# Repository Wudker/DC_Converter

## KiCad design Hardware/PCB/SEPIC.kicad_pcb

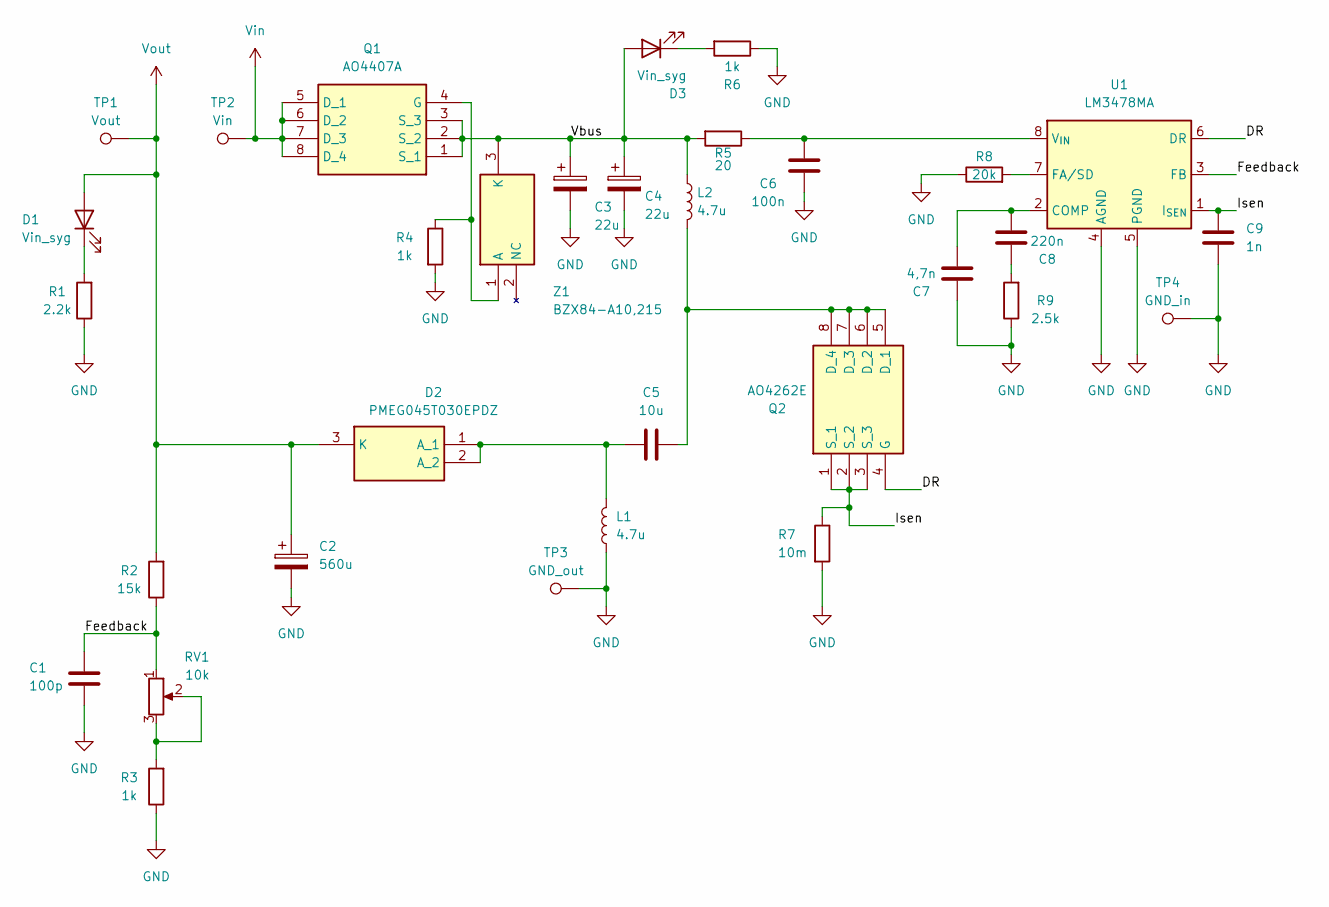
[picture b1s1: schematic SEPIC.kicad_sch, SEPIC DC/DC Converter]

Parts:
C1: 100p; C_1206_3216Metric
C2: 560u; CP_Elec_8x10
C3, C4: 22u; CP_Elec_6.3x5.8
C5: 10u; C_1206_3216Metric
C6: 100n; C_1206_3216Metric
C7: 4,7n; C_1206_3216Metric
C8: 220n; C_1206_3216Metric
C9: 1n; C_1206_3216Metric
D1, D3: Vin_syg; LED_1206_3216Metric
D2: PMEG045T030EPDZ; Nexperia_CFP15_SOT-1289; Manufacturer_Part_Number PMEG045T030EPDZ
L1, L2: 4.7u; INDPM7166X300N
Q1: AO4407A; SOIC-8_3.9x4.9mm_P1.27mm; Manufacturer_Part_Number AO4407A
Q2: AO4262E; SOIC-8_3.9x4.9mm_P1.27mm; Manufacturer_Part_Number AO4262E
R1: 2.2k; R_1206_3216Metric
R2: 15k; R_1206_3216Metric
R3, R4, R6: 1k; R_1206_3216Metric
R5: 20; R_1206_3216Metric
R7: 10m; R_1206_3216Metric
R8: 20k; R_1206_3216Metric
R9: 2.5k; R_1206_3216Metric
RV1: 10k; Potentiometer_Bourns_3296W_Vertical
TP1: Vout; TestPoint_Plated_Hole_D2.0mm
TP2: Vin; TestPoint_Plated_Hole_D2.0mm
TP3: GND_out; TestPoint_THTPad_4.0x4.0mm_Drill2.0mm
TP4: GND_in; TestPoint_THTPad_4.0x4.0mm_Drill2.0mm
U1: LM3478MA; SOIC-8_3.9x4.9mm_P1.27mm
Z1: BZX84-A10,215; SOT-23; Manufacturer_Part_Number BZX84-A10,215

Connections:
/DR: Q2.4 (G), U1.6 (DR)
/Feedback: C1.2, R2.1, RV1.1, U1.3 (FB)
/Isen: C9.2, Q2.1 (S_1), Q2.2 (S_2), Q2.3 (S_3), R7.1, U1.1 (I_{SEN})
/Vbus: C3.1, C4.1, D3.2 (A), L2.1, Q1.1 (S_1), Q1.2 (S_2), Q1.3 (S_3), R5.2, Z1.3 (K)
GND: C1.1, C2.2, C3.2, C4.2, C6.2, C7.1, C9.1, L1.1, R1.1, R3.1, R4.2, R6.1, R7.2, R8.1, R9.1, TP3.1 (1_1), TP4.1 (1_1), U1.4 (AGND), U1.5 (PGND)
unnamed: C8.1, R9.2
unnamed: D1.1 (K), R1.2
unnamed: C5.1, D2.1 (A_1), D2.2 (A_2), L1.2
unnamed: D3.1 (K), R6.2
unnamed: Q1.4 (G), R4.1, Z1.1 (A)
unnamed: C5.2, L2.2, Q2.5 (D_1), Q2.6 (D_2), Q2.7 (D_3), Q2.8 (D_4)
unnamed: R3.2, RV1.2, RV1.3
unnamed: C7.2, C8.2, U1.2 (COMP)
unnamed: R8.2, U1.7 (FA/SD)
unnamed: C6.1, R5.1, U1.8 (V_{IN})
Vin: Q1.5 (D_1), Q1.6 (D_2), Q1.7 (D_3), Q1.8 (D_4), TP2.1 (1_1)
Vout: C2.1, D1.2 (A), D2.3 (K), R2.2, TP1.1 (1_1)

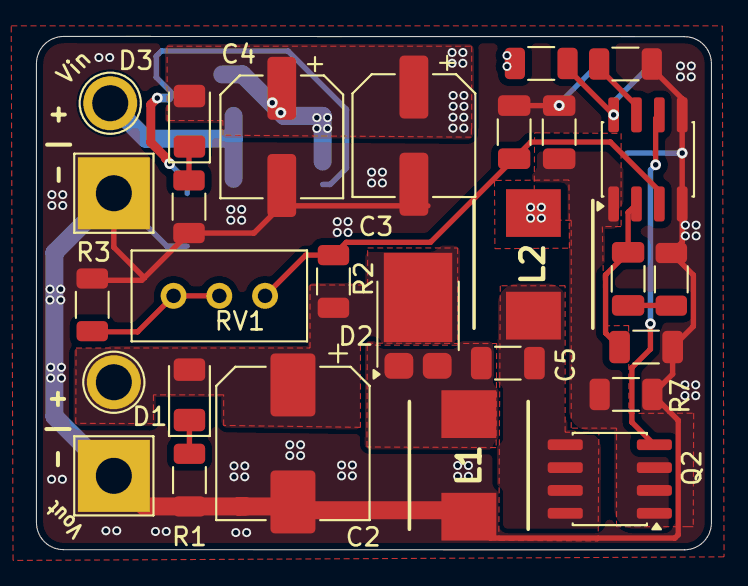
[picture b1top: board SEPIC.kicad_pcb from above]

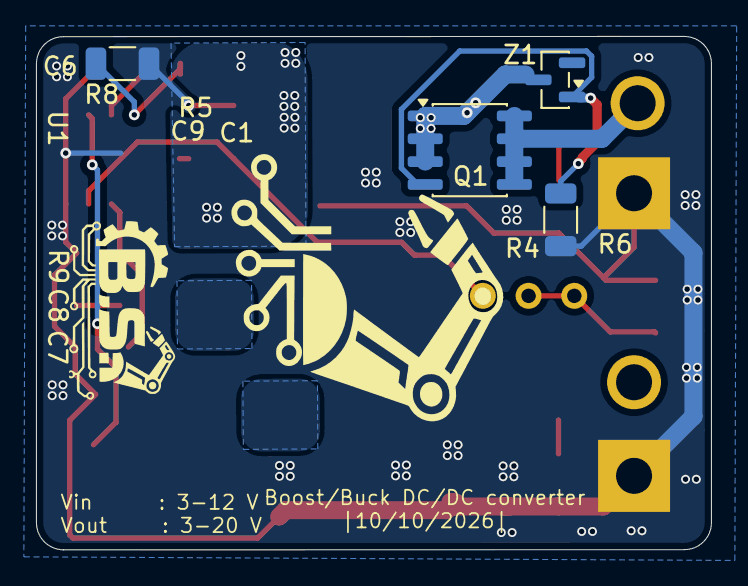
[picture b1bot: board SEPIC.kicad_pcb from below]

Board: 2 copper layers, 37.5 x 28.5 mm, 32 parts (4 on the bottom side), 17 nets.
